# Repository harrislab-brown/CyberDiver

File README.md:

# CyberDiver: an untethered cyber-physical robotic impactor for water-entry experiments

This repository provides design source files and raw data to complement the article ([https://arxiv.org/abs/2503.20702](https://arxiv.org/abs/2503.20702)). 

# License

CyberDiver is licensed under the CC BY-SA 4.0 Creative Commons license.

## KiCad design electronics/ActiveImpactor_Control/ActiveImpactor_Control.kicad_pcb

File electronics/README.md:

# Electronics

This directory contains the KiCad design files, schematics, and Gerber files for the custom PCBs used in the CyberDiver. The control board and power board implement the majority of the functionality. The encoder daughterboard provides nose displacement measurements with an optical linear encoder (Celera CE300-40). The nose accelerometer board provides direct measurements of the impactor nose acceleration.

## Control board

## Power board

## Encoder daughter board

## Accelerometer daughter board

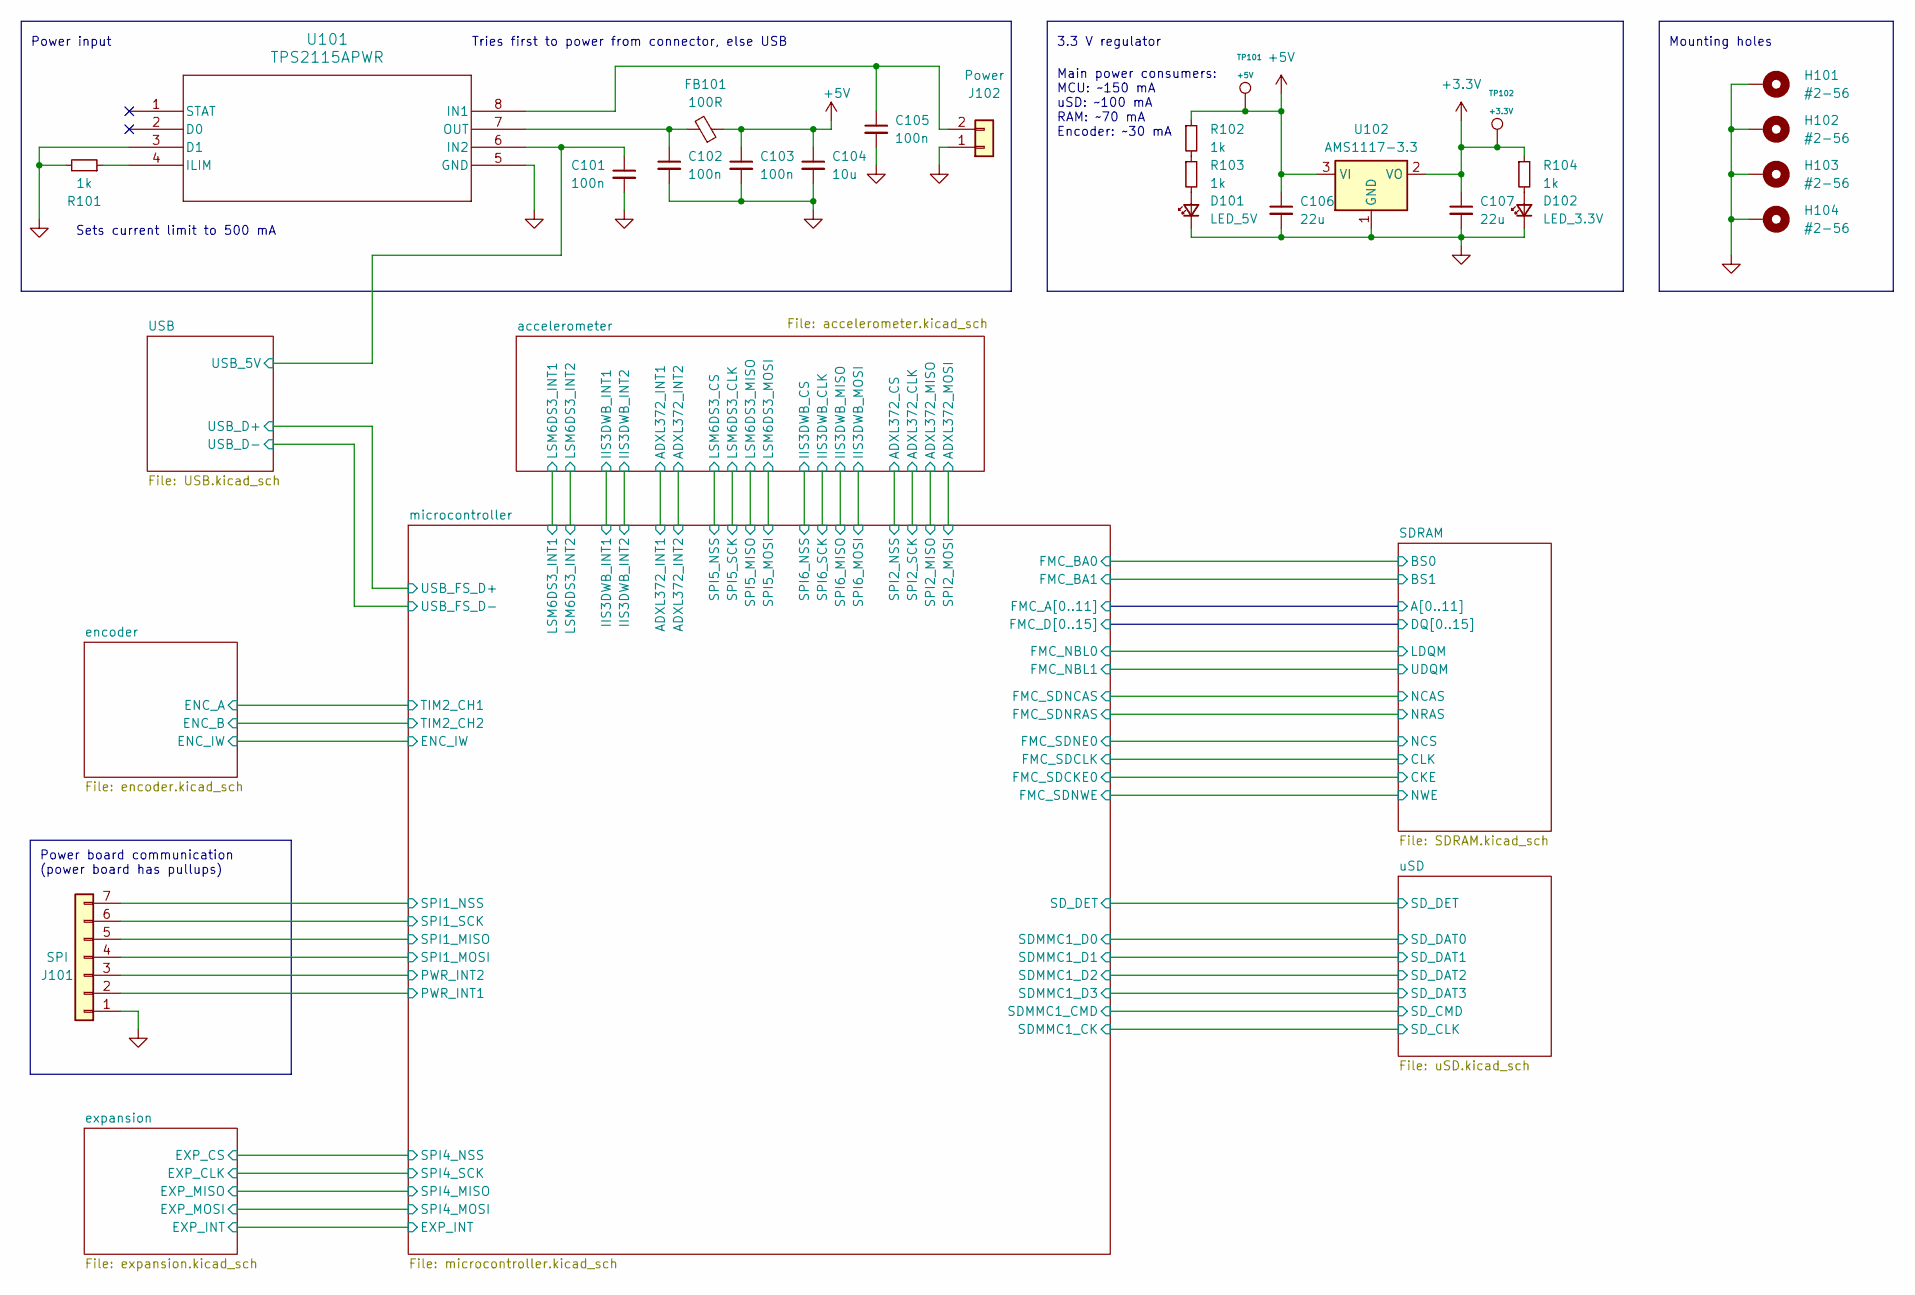
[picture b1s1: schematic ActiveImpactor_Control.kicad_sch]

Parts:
C101, C102, C103, C105: 100n; C_0402_1005Metric; LCSC C1525
C104: 10u; C_0603_1608Metric; LCSC C19702
C106, C107: 22u; C_0603_1608Metric; LCSC C2762594
D101: LED_5V; LED_0603_1608Metric; LCSC C965805
D102: LED_3.3V; LED_0603_1608Metric; LCSC C965805
FB101: 100R; L_0603_1608Metric; LCSC C1002
H101, H102, H103, H104: #2-56; MountingHole_2.5mm_Pad
J101: SPI; JST_SH_BM07B-SRSS-TB_1x07-1MP_P1.00mm_Vertical; Digikey 455-BM07B-SRSS-TBCT-ND
J102: Power; JST_PH_B2B-PH-SM4-TB_1x02-1MP_P2.00mm_Vertical; Digikey 455-B2B-PH-SM4-TBCT-ND
R101, R102, R103, R104: 1k; R_0402_1005Metric; LCSC C11702
TP101: +5V; TestPoint_Pad_D1.0mm
TP102: +3.3V; TestPoint_Pad_D1.0mm
U101: TPS2115APWR; TSSOP-8_4.4x3mm_P0.65mm; LCSC C70287
U102: AMS1117-3.3; SOT-223-3_TabPin2; LCSC C6186

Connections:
+3.3V: C107.1, R104.1, TP102.1, U102.2 (VO); also elsewhere on the board
+5V: C103.1, C104.1, C106.1, FB101.1, R102.1, TP101.1, U102.3 (VI); also elsewhere on the board
/USB/USB_5V: C101.1, U101.6 (IN2); also elsewhere on the board
/microcontroller/PWR_INT1: J101.2; also elsewhere on the board
/microcontroller/PWR_INT2: J101.3; also elsewhere on the board
/microcontroller/SPI1_MISO: J101.5; also elsewhere on the board
/microcontroller/SPI1_MOSI: J101.4; also elsewhere on the board
/microcontroller/SPI1_NSS: J101.7; also elsewhere on the board
/microcontroller/SPI1_SCK: J101.6; also elsewhere on the board
GND: C101.2, C102.2, C103.2, C104.2, C105.2, C106.2, C107.2, D101.1 (K), D102.1 (K), H101.1, H102.1, H103.1, H104.1, J101.1, J102.1, R101.2, U101.3 (D1), U101.5 (GND), U102.1 (GND); also elsewhere on the board
unnamed: D101.2 (A), R103.2
unnamed: D102.2 (A), R104.2
unnamed: C105.1, J102.2, U101.8 (IN1)
unnamed: R102.2, R103.1
unnamed: R101.1, U101.4 (ILIM)
unnamed: C102.1, FB101.2, U101.7 (OUT)

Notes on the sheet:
Mounting holes
Power input
Power board communication (power board has pullups)
Tries first to power from connector, else USB
Main power consumers: MCU: ~150 mA uSD: ~100 mA RAM: ~70 mA Encoder: ~30 mA
3.3 V regulator
Sets current limit to 500 mA

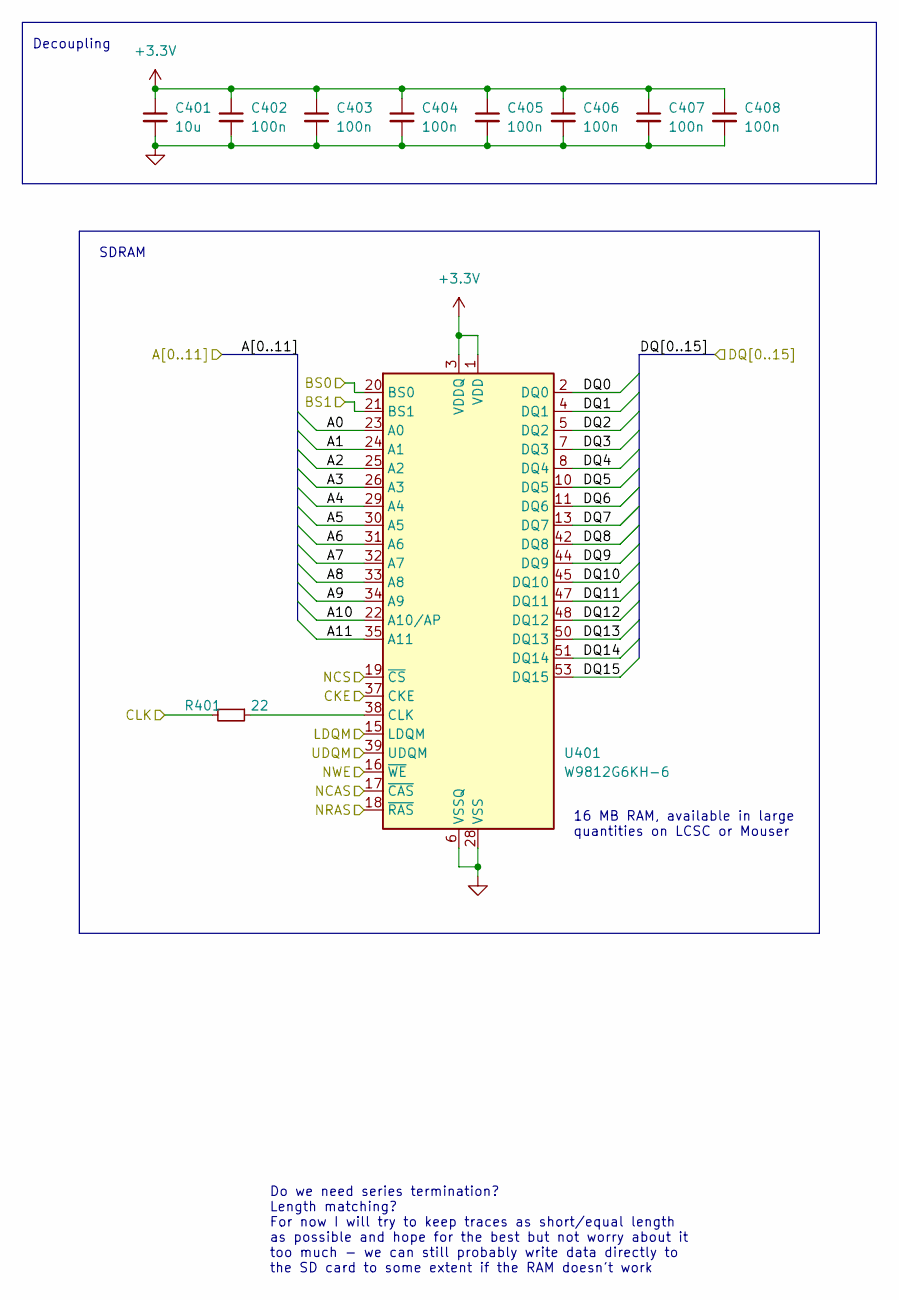
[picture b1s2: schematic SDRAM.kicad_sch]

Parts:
C401: 10u; C_0603_1608Metric; LCSC C19702
C402, C403, C404, C405, C406, C407, C408: 100n; C_0402_1005Metric; LCSC C1525
R401: 22; R_0402_1005Metric; LCSC C25092
U401: W9812G6KH-6; TSOP-II-54_22.2x10.16mm_P0.8mm; LCSC C62379

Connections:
+3.3V: C401.1, C402.1, C403.1, C404.1, C405.1, C406.1, C407.1, C408.1, U401.1 (VDD), U401.3 (VDDQ), U401.9 (VDDQ), U401.14 (VDD), U401.27 (VDD), U401.43 (VDDQ), U401.49 (VDDQ); also elsewhere on the board
/SDRAM/A0: U401.23 (A0); also elsewhere on the board
/SDRAM/A1: U401.24 (A1); also elsewhere on the board
/SDRAM/A2: U401.25 (A2); also elsewhere on the board
/SDRAM/A3: U401.26 (A3); also elsewhere on the board
/SDRAM/A4: U401.29 (A4); also elsewhere on the board
/SDRAM/A5: U401.30 (A5); also elsewhere on the board
/SDRAM/A6: U401.31 (A6); also elsewhere on the board
/SDRAM/A7: U401.32 (A7); also elsewhere on the board
/SDRAM/A8: U401.33 (A8); also elsewhere on the board
/SDRAM/A9: U401.34 (A9); also elsewhere on the board
/SDRAM/A10: U401.22 (A10/AP); also elsewhere on the board
/SDRAM/A11: U401.35 (A11); also elsewhere on the board
/SDRAM/BS0: U401.20 (BS0); also elsewhere on the board
/SDRAM/BS1: U401.21 (BS1); also elsewhere on the board
/SDRAM/CKE: U401.37 (CKE); also elsewhere on the board
/SDRAM/CLK: R401.2; also elsewhere on the board
/SDRAM/DQ0: U401.2 (DQ0); also elsewhere on the board
/SDRAM/DQ1: U401.4 (DQ1); also elsewhere on the board
/SDRAM/DQ2: U401.5 (DQ2); also elsewhere on the board
/SDRAM/DQ3: U401.7 (DQ3); also elsewhere on the board
/SDRAM/DQ4: U401.8 (DQ4); also elsewhere on the board
/SDRAM/DQ5: U401.10 (DQ5); also elsewhere on the board
/SDRAM/DQ6: U401.11 (DQ6); also elsewhere on the board
/SDRAM/DQ7: U401.13 (DQ7); also elsewhere on the board
/SDRAM/DQ8: U401.42 (DQ8); also elsewhere on the board
/SDRAM/DQ9: U401.44 (DQ9); also elsewhere on the board
/SDRAM/DQ10: U401.45 (DQ10); also elsewhere on the board
/SDRAM/DQ11: U401.47 (DQ11); also elsewhere on the board
/SDRAM/DQ12: U401.48 (DQ12); also elsewhere on the board
/SDRAM/DQ13: U401.50 (DQ13); also elsewhere on the board
/SDRAM/DQ14: U401.51 (DQ14); also elsewhere on the board
/SDRAM/DQ15: U401.53 (DQ15); also elsewhere on the board
/SDRAM/LDQM: U401.15 (LDQM); also elsewhere on the board
/SDRAM/NCAS: U401.17 (~CAS); also elsewhere on the board
/SDRAM/NCS: U401.19 (~CS); also elsewhere on the board
/SDRAM/NRAS: U401.18 (~RAS); also elsewhere on the board
/SDRAM/NWE: U401.16 (~WE); also elsewhere on the board
/SDRAM/UDQM: U401.39 (UDQM); also elsewhere on the board
GND: C401.2, C402.2, C403.2, C404.2, C405.2, C406.2, C407.2, C408.2, U401.6 (VSSQ), U401.12 (VSSQ), U401.28 (VSS), U401.41 (VSS), U401.46 (VSSQ), U401.52 (VSSQ), U401.54 (VSS); also elsewhere on the board
unnamed: R401.1, U401.38 (CLK)

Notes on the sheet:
SDRAM
Do we need series termination? Length matching? For now I will try to keep traces as short/equal length as possible and hope for the best but not worry about it too much - we can still probably write data directly to the SD card to some extent if the RAM doesn't work
16 MB RAM, available in large quantities on LCSC or Mouser
Decoupling

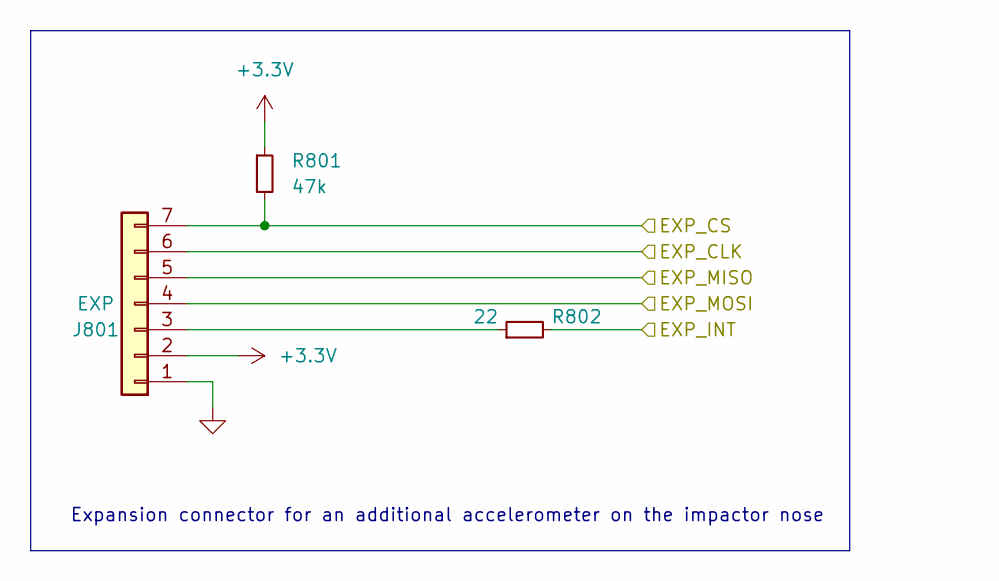
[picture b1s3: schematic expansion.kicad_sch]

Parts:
J801: EXP; JST_SH_SM07B-SRSS-TB_1x07-1MP_P1.00mm_Horizontal; LCSC C160406
R801: 47k; R_0402_1005Metric; LCSC C25792
R802: 22; R_0402_1005Metric; LCSC C25092

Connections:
+3.3V: J801.2, R801.1; also elsewhere on the board
/expansion/EXP_CLK: J801.6; also elsewhere on the board
/expansion/EXP_CS: J801.7, R801.2; also elsewhere on the board
/expansion/EXP_INT: R802.2; also elsewhere on the board
/expansion/EXP_MISO: J801.5; also elsewhere on the board
/expansion/EXP_MOSI: J801.4; also elsewhere on the board
GND: J801.1; also elsewhere on the board
unnamed: J801.3, R802.1

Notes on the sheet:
Expansion connector for an additional accelerometer on the impactor nose

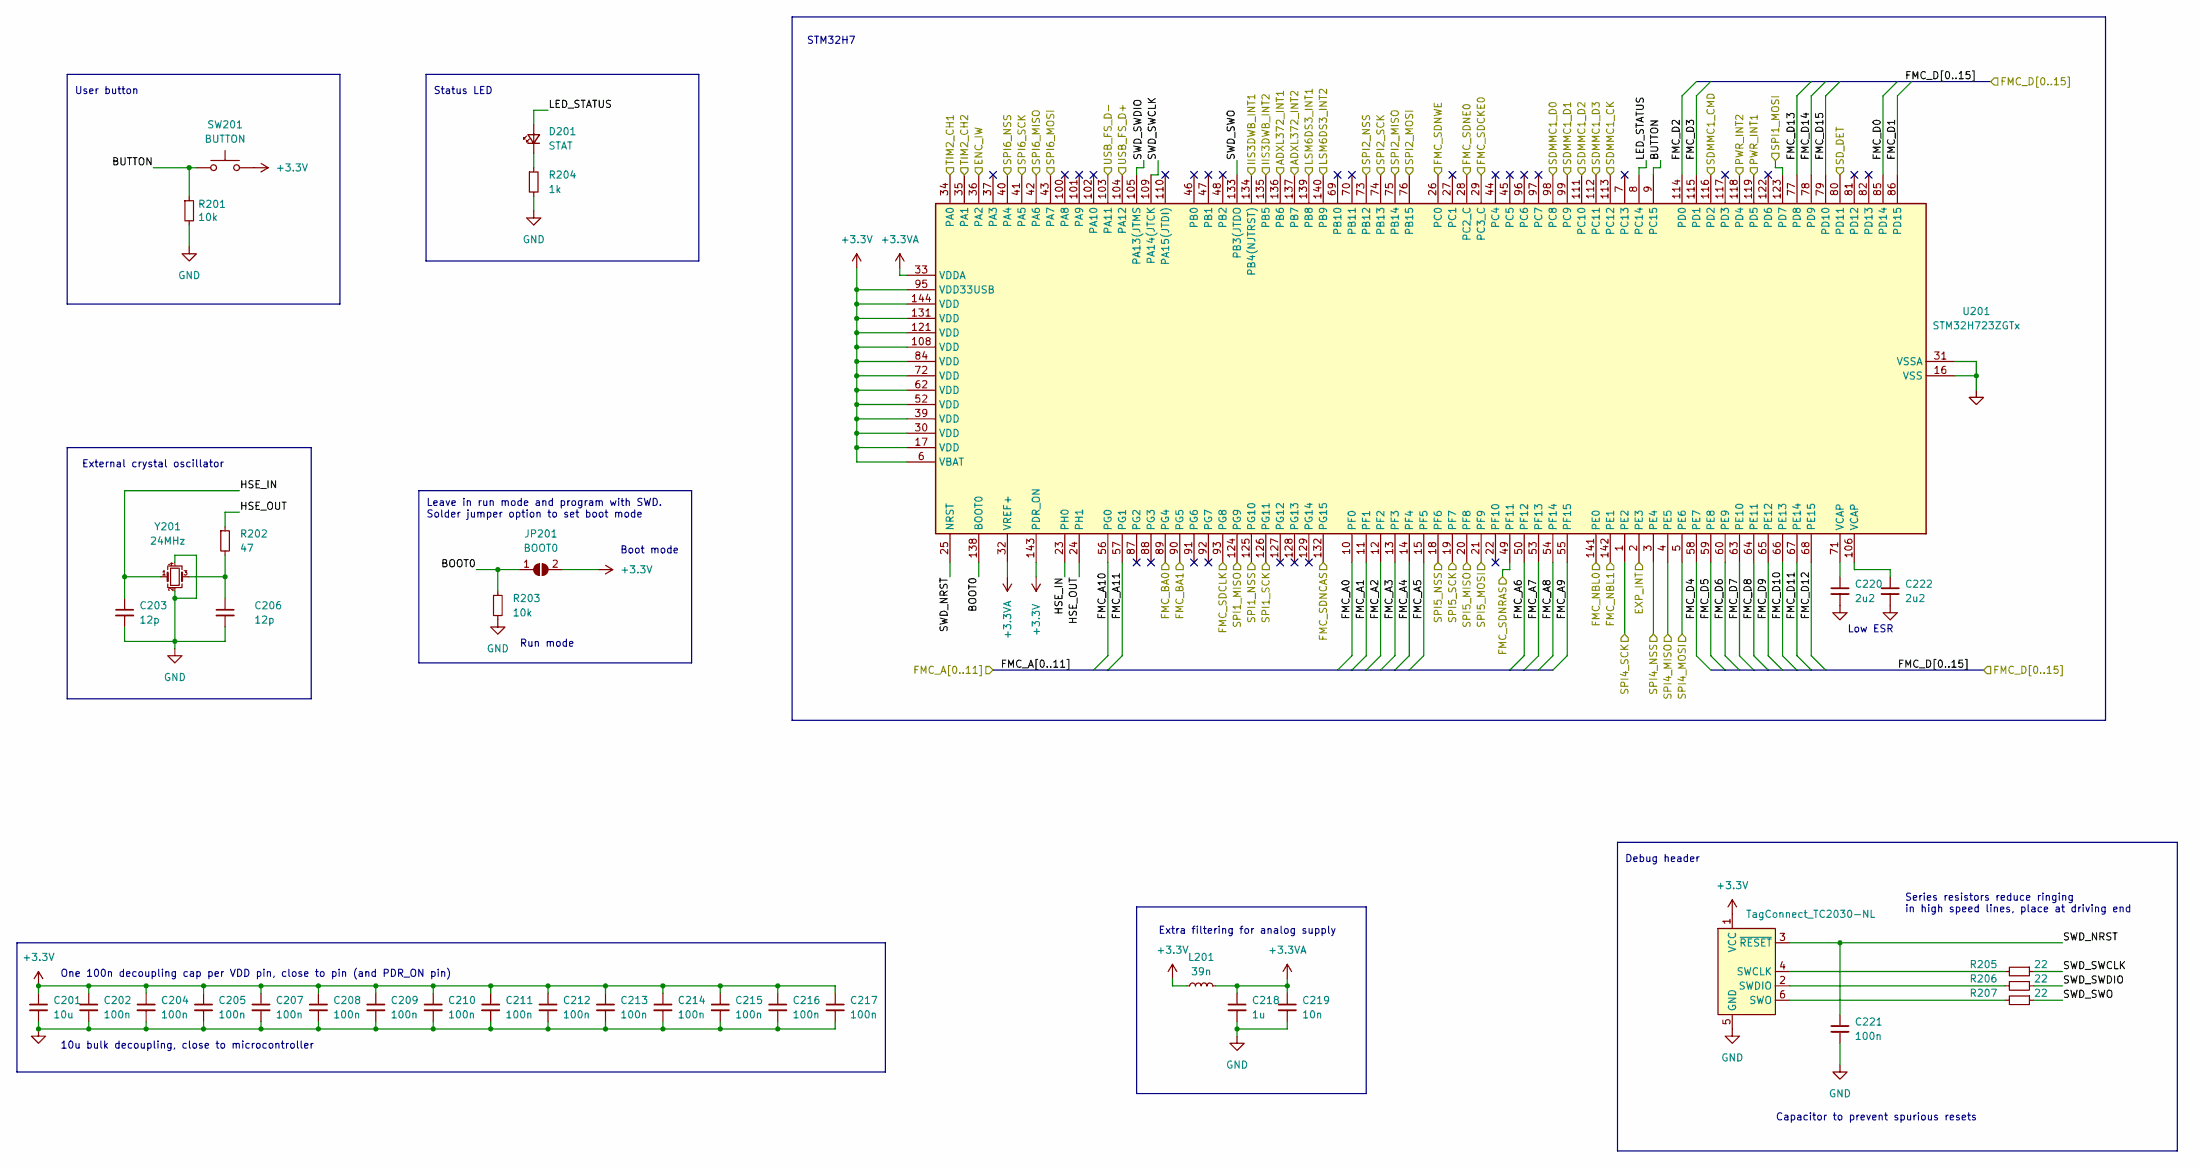
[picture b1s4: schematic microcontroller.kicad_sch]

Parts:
C201: 10u; C_0603_1608Metric; LCSC C19702
C202, C204, C205, C207, C208, C209, C210, C211, C212, C213, C214, C215, C216, C217, C221: 100n; C_0402_1005Metric; LCSC C1525
C203, C206: 12p; C_0402_1005Metric; LCSC C1547
C218: 1u; C_0402_1005Metric; LCSC C52923
C219: 10n; C_0402_1005Metric; LCSC C15195
C220, C222: 2u2; C_0603_1608Metric; LCSC C23630
D201: STAT; LED_0603_1608Metric; LCSC C84266
J201: TagConnect_TC2030-NL; Tag-Connect_TC2030-IDC-NL_2x03_P1.27mm_Vertical
JP201: BOOT0; SolderJumper-2_P1.3mm_Open_RoundedPad1.0x1.5mm
L201: 39n; L_0402_1005Metric; LCSC C26443
R201, R203: 10k; R_0402_1005Metric; LCSC C25744
R202: 47; R_0402_1005Metric; LCSC C25118
R204: 1k; R_0402_1005Metric; LCSC C11702
R205, R206, R207: 22; R_0402_1005Metric; LCSC C25092
SW201: BUTTON; SW_Push_SPST_NO_Alps_SKRK; LCSC C202388
U201: STM32H723ZGTx; LQFP-144_20x20mm_P0.5mm; LCSC C730146
Y201: 24MHz; Crystal_SMD_3225-4Pin_3.2x2.5mm; LCSC C70590

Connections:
+3.3V: C201.1, C202.1, C204.1, C205.1, C207.1, C208.1, C209.1, C210.1, C211.1, C212.1, C213.1, C214.1, C215.1, C216.1, C217.1, J201.1 (VCC), JP201.2 (B), L201.1, SW201.2, U201.6 (VBAT), U201.17 (VDD), U201.30 (VDD), U201.39 (VDD), U201.52 (VDD), U201.62 (VDD), U201.72 (VDD), U201.84 (VDD), U201.95 (VDD33USB), U201.108 (VDD), U201.121 (VDD), U201.131 (VDD), U201.143 (PDR_ON), U201.144 (VDD); also elsewhere on the board
+3.3VA: C218.1, C219.1, L201.2, U201.32 (VREF+), U201.33 (VDDA)
/SDRAM/A0: U201.10 (PF0); also elsewhere on the board
/SDRAM/A1: U201.11 (PF1); also elsewhere on the board
/SDRAM/A2: U201.12 (PF2); also elsewhere on the board
/SDRAM/A3: U201.13 (PF3); also elsewhere on the board
/SDRAM/A4: U201.14 (PF4); also elsewhere on the board
/SDRAM/A5: U201.15 (PF5); also elsewhere on the board
/SDRAM/A6: U201.50 (PF12); also elsewhere on the board
/SDRAM/A7: U201.53 (PF13); also elsewhere on the board
/SDRAM/A8: U201.54 (PF14); also elsewhere on the board
/SDRAM/A9: U201.55 (PF15); also elsewhere on the board
/SDRAM/A10: U201.56 (PG0); also elsewhere on the board
/SDRAM/A11: U201.57 (PG1); also elsewhere on the board
/SDRAM/BS0: U201.89 (PG4); also elsewhere on the board
/SDRAM/BS1: U201.90 (PG5); also elsewhere on the board
/SDRAM/CKE: U201.29 (PC3_C); also elsewhere on the board
/SDRAM/CLK: U201.93 (PG8); also elsewhere on the board
/SDRAM/DQ0: U201.85 (PD14); also elsewhere on the board
/SDRAM/DQ1: U201.86 (PD15); also elsewhere on the board
/SDRAM/DQ2: U201.114 (PD0); also elsewhere on the board
/SDRAM/DQ3: U201.115 (PD1); also elsewhere on the board
/SDRAM/DQ4: U201.58 (PE7); also elsewhere on the board
/SDRAM/DQ5: U201.59 (PE8); also elsewhere on the board
/SDRAM/DQ6: U201.60 (PE9); also elsewhere on the board
/SDRAM/DQ7: U201.63 (PE10); also elsewhere on the board
/SDRAM/DQ8: U201.64 (PE11); also elsewhere on the board
/SDRAM/DQ9: U201.65 (PE12); also elsewhere on the board
/SDRAM/DQ10: U201.66 (PE13); also elsewhere on the board
/SDRAM/DQ11: U201.67 (PE14); also elsewhere on the board
/SDRAM/DQ12: U201.68 (PE15); also elsewhere on the board
/SDRAM/DQ13: U201.77 (PD8); also elsewhere on the board
/SDRAM/DQ14: U201.78 (PD9); also elsewhere on the board
/SDRAM/DQ15: U201.79 (PD10); also elsewhere on the board
/SDRAM/LDQM: U201.141 (PE0); also elsewhere on the board
/SDRAM/NCAS: U201.132 (PG15); also elsewhere on the board
/SDRAM/NCS: U201.28 (PC2_C); also elsewhere on the board
/SDRAM/NRAS: U201.49 (PF11); also elsewhere on the board
/SDRAM/NWE: U201.26 (PC0); also elsewhere on the board
/SDRAM/UDQM: U201.142 (PE1); also elsewhere on the board
/USB/USB_D+: U201.104 (PA12); also elsewhere on the board
/USB/USB_D-: U201.103 (PA11); also elsewhere on the board
/accelerometer/ADXL372_CLK: U201.74 (PB13); also elsewhere on the board
/accelerometer/ADXL372_CS: U201.73 (PB12); also elsewhere on the board
/accelerometer/ADXL372_INT1: U201.136 (PB6); also elsewhere on the board
/accelerometer/ADXL372_INT2: U201.137 (PB7); also elsewhere on the board
/accelerometer/ADXL372_MISO: U201.75 (PB14); also elsewhere on the board
/accelerometer/ADXL372_MOSI: U201.76 (PB15); also elsewhere on the board
/accelerometer/IIS3DWB_CLK: U201.41 (PA5); also elsewhere on the board
/accelerometer/IIS3DWB_CS: U201.40 (PA4); also elsewhere on the board
/accelerometer/IIS3DWB_INT1: U201.134 (PB4(NJTRST)); also elsewhere on the board
/accelerometer/IIS3DWB_INT2: U201.135 (PB5); also elsewhere on the board
/accelerometer/IIS3DWB_MISO: U201.42 (PA6); also elsewhere on the board
/accelerometer/IIS3DWB_MOSI: U201.43 (PA7); also elsewhere on the board
/accelerometer/LSM6DS3_CLK: U201.19 (PF7); also elsewhere on the board
/accelerometer/LSM6DS3_CS: U201.18 (PF6); also elsewhere on the board
/accelerometer/LSM6DS3_INT1: U201.139 (PB8); also elsewhere on the board
/accelerometer/LSM6DS3_INT2: U201.140 (PB9); also elsewhere on the board
/accelerometer/LSM6DS3_MISO: U201.20 (PF8); also elsewhere on the board
/accelerometer/LSM6DS3_MOSI: U201.21 (PF9); also elsewhere on the board
/encoder/ENC_A: U201.34 (PA0); also elsewhere on the board
/encoder/ENC_B: U201.35 (PA1); also elsewhere on the board
/encoder/ENC_IW: U201.36 (PA2); also elsewhere on the board
/expansion/EXP_CLK: U201.1 (PE2); also elsewhere on the board
/expansion/EXP_CS: U201.3 (PE4); also elsewhere on the board
/expansion/EXP_INT: U201.2 (PE3); also elsewhere on the board
/expansion/EXP_MISO: U201.4 (PE5); also elsewhere on the board
/expansion/EXP_MOSI: U201.5 (PE6); also elsewhere on the board
/microcontroller/BOOT0: JP201.1 (A), R203.1, U201.138 (BOOT0)
/microcontroller/BUTTON: R201.1, SW201.1, U201.9 (PC15)
/microcontroller/HSE_IN: C203.1, U201.23 (PH0), Y201.1
/microcontroller/HSE_OUT: R202.1, U201.24 (PH1)
/microcontroller/LED_STATUS: D201.2 (A), U201.8 (PC14)
/microcontroller/PWR_INT1: U201.119 (PD5); also elsewhere on the board
/microcontroller/PWR_INT2: U201.118 (PD4); also elsewhere on the board
/microcontroller/SDMMC1_CK: U201.113 (PC12); also elsewhere on the board
/microcontroller/SDMMC1_CMD: U201.116 (PD2); also elsewhere on the board
/microcontroller/SDMMC1_D0: U201.98 (PC8); also elsewhere on the board
/microcontroller/SDMMC1_D1: U201.99 (PC9); also elsewhere on the board
/microcontroller/SDMMC1_D2: U201.111 (PC10); also elsewhere on the board
/microcontroller/SDMMC1_D3: U201.112 (PC11); also elsewhere on the board
/microcontroller/SD_DET: U201.80 (PD11); also elsewhere on the board
/microcontroller/SPI1_MISO: U201.124 (PG9); also elsewhere on the board
/microcontroller/SPI1_MOSI: U201.123 (PD7); also elsewhere on the board
/microcontroller/SPI1_NSS: U201.125 (PG10); also elsewhere on the board
/microcontroller/SPI1_SCK: U201.126 (PG11); also elsewhere on the board
/microcontroller/SWD_NRST: C221.1, J201.3 (~RESET), U201.25 (NRST)
/microcontroller/SWD_SWCLK: R205.1, U201.109 (PA14(JTCK)
/microcontroller/SWD_SWDIO: R206.1, U201.105 (PA13(JTMS)
/microcontroller/SWD_SWO: R207.1, U201.133 (PB3(JTDO)
GND: C201.2, C202.2, C203.2, C204.2, C205.2, C206.2, C207.2, C208.2, C209.2, C210.2, C211.2, C212.2, C213.2, C214.2, C215.2, C216.2, C217.2, C218.2, C219.2, C220.2, C221.2, C222.2, J201.5 (GND), R201.2, R203.2, R204.2, U201.16 (VSS), U201.31 (VSSA), U201.38 (VSS), U201.51 (VSS), U201.61 (VSS), U201.83 (VSS), U201.94 (VSS), U201.107 (VSS), U201.120 (VSS), U201.130 (VSS), Y201.2, Y201.4; also elsewhere on the board
unnamed: C206.1, R202.2, Y201.3
unnamed: C220.1, U201.71 (VCAP)
unnamed: C222.1, U201.106 (VCAP)
unnamed: D201.1 (K), R204.1
unnamed: J201.4 (SWCLK), R205.2
unnamed: J201.2 (SWDIO), R206.2
unnamed: J201.6 (SWO), R207.2

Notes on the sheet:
Debug header
Run mode
Leave in run mode and program with SWD. Solder jumper option to set boot mode
User button
Low ESR
Extra filtering for analog supply
One 100n decoupling cap per VDD pin, close to pin (and PDR_ON pin)
Boot mode
Status LED
External crystal oscillator
Capacitor to prevent spurious resets
STM32H7
Series resistors reduce ringing in high speed lines, place at driving end
10u bulk decoupling, close to microcontroller

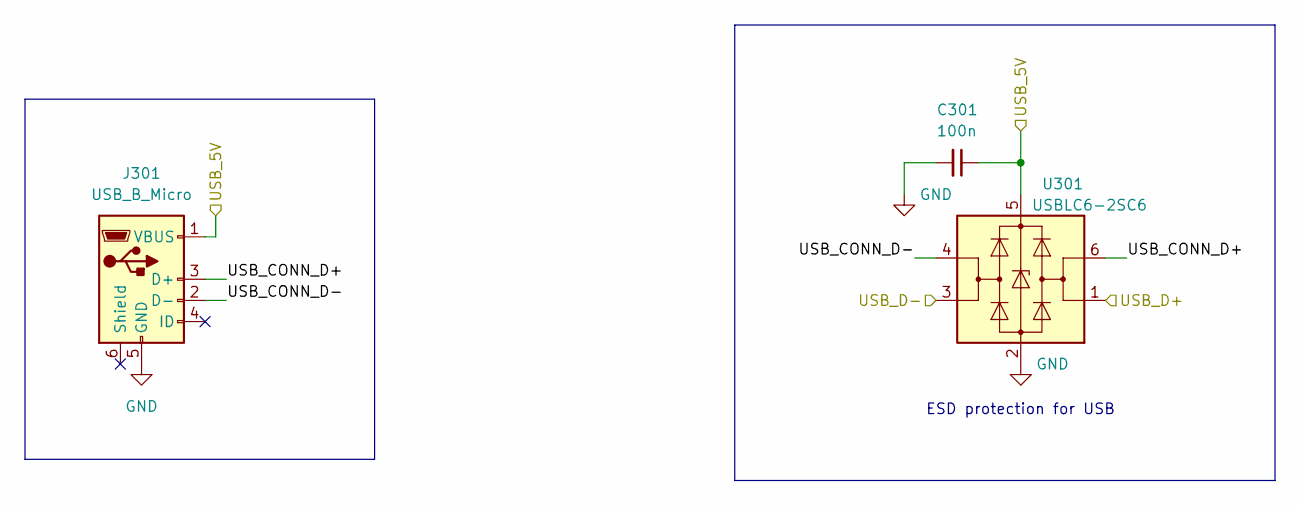
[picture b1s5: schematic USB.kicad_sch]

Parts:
C301: 100n; C_0402_1005Metric; LCSC C1525
J301: USB_B_Micro; MicroXNJ; LCSC C404969
U301: USBLC6-2SC6; SOT-23-6; LCSC C2827654

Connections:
/USB/USB_5V: C301.1, J301.1 (VBUS), U301.5 (VBUS); also elsewhere on the board
/USB/USB_CONN_D+: J301.3 (D+), U301.6 (I/O1)
/USB/USB_CONN_D-: J301.2 (D-), U301.4 (I/O2)
/USB/USB_D+: U301.1 (I/O1); also elsewhere on the board
/USB/USB_D-: U301.3 (I/O2); also elsewhere on the board
GND: C301.2, J301.5 (GND), U301.2 (GND); also elsewhere on the board

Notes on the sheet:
ESD protection for USB

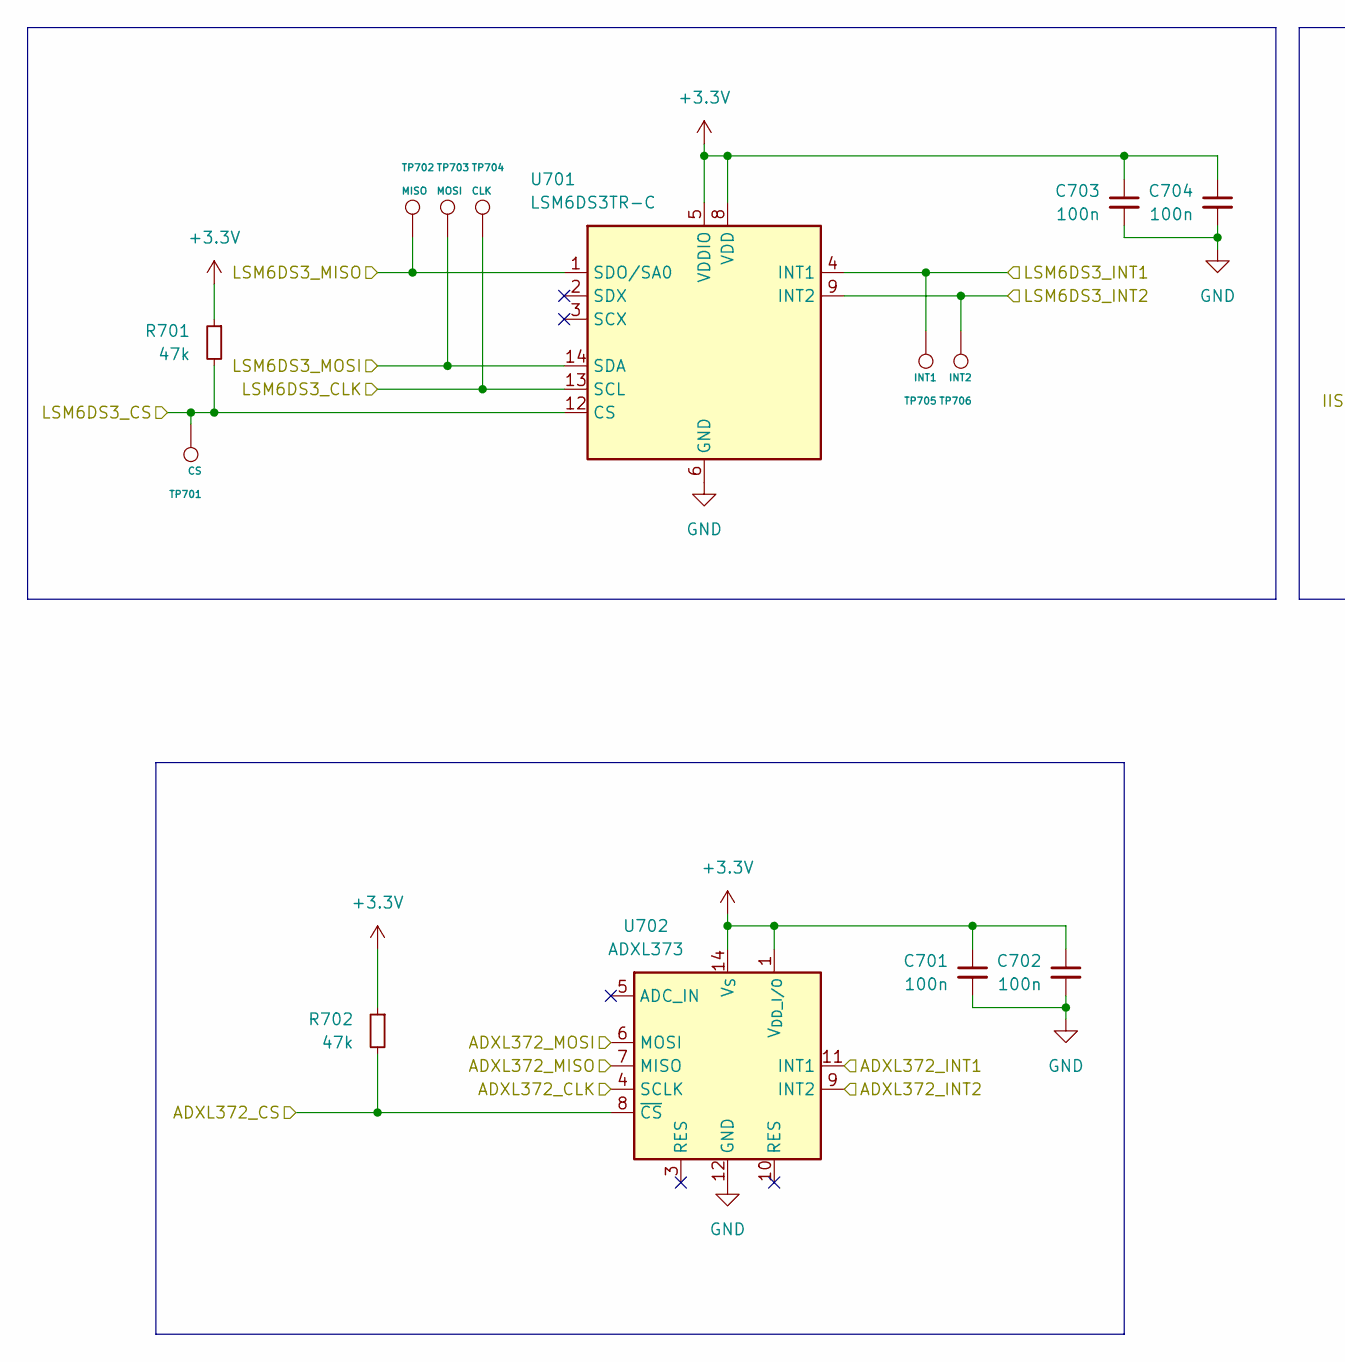
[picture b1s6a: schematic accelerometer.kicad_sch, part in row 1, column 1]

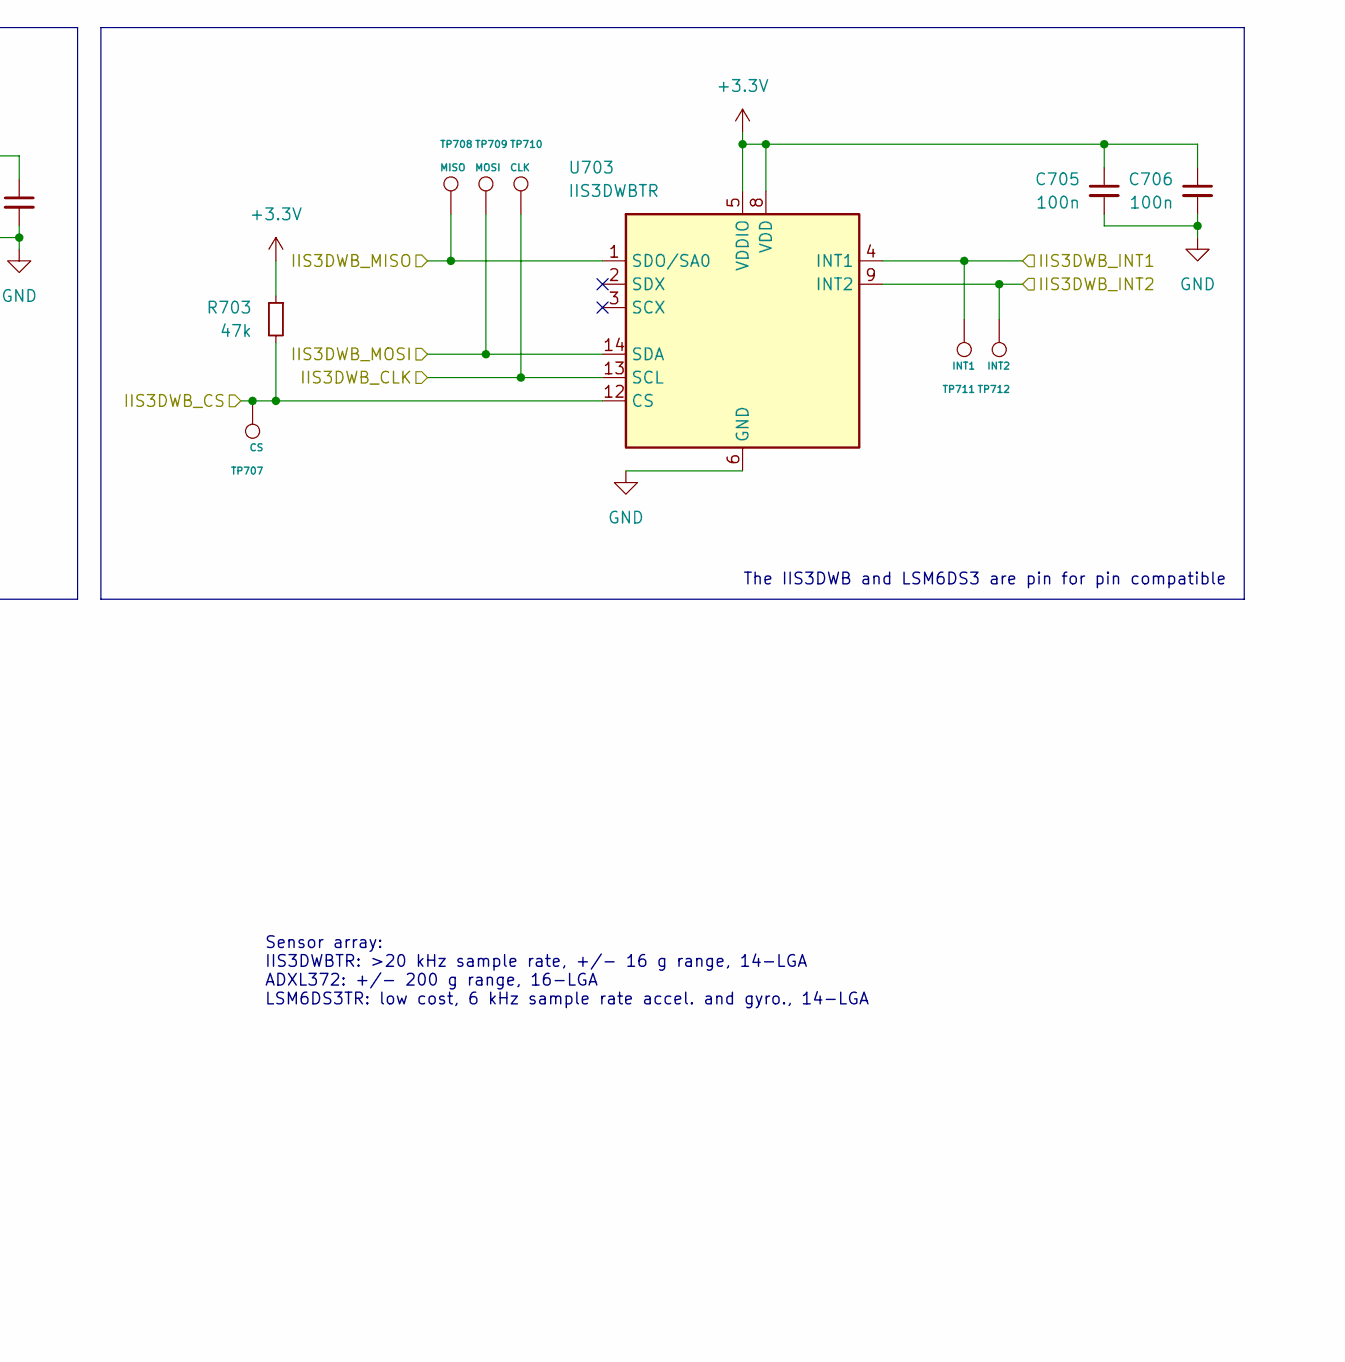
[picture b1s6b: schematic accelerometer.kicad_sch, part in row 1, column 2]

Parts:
C701, C702, C703, C704, C705, C706: 100n; C_0402_1005Metric; LCSC C1525
R701, R702, R703: 47k; R_0402_1005Metric; LCSC C25792
TP701, TP707: CS; TestPoint_Pad_D1.0mm
TP702, TP708: MISO; TestPoint_Pad_D1.0mm
TP703, TP709: MOSI; TestPoint_Pad_D1.0mm
TP704, TP710: CLK; TestPoint_Pad_D1.0mm
TP705, TP711: INT1; TestPoint_Pad_D1.0mm
TP706, TP712: INT2; TestPoint_Pad_D1.0mm
U701: LSM6DS3TR-C; LGA-14_3x2.5mm_P0.5mm_LayoutBorder3x4y; LCSC C967633
U702: ADXL373; Analog_LGA-16_3.25x3mm_P0.5mm_LayoutBorder3x5y; LCSC C3216386
U703: IIS3DWBTR; LGA-14_3x2.5mm_P0.5mm_LayoutBorder3x4y; LCSC C717702

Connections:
+3.3V: C701.1, C702.1, C703.1, C704.1, C705.1, C706.1, R701.1, R702.1, R703.1, U701.5 (VDDIO), U701.8 (VDD), U702.1 (V_{DD_I/O}), U702.14 (V_{S}), U703.5 (VDDIO), U703.8 (VDD); also elsewhere on the board
/accelerometer/ADXL372_CLK: U702.4 (SCLK); also elsewhere on the board
/accelerometer/ADXL372_CS: R702.2, U702.8 (~CS); also elsewhere on the board
/accelerometer/ADXL372_INT1: U702.11 (INT1); also elsewhere on the board
/accelerometer/ADXL372_INT2: U702.9 (INT2); also elsewhere on the board
/accelerometer/ADXL372_MISO: U702.7 (MISO); also elsewhere on the board
/accelerometer/ADXL372_MOSI: U702.6 (MOSI); also elsewhere on the board
/accelerometer/IIS3DWB_CLK: TP710.1, U703.13 (SCL); also elsewhere on the board
/accelerometer/IIS3DWB_CS: R703.2, TP707.1, U703.12 (CS); also elsewhere on the board
/accelerometer/IIS3DWB_INT1: TP711.1, U703.4 (INT1); also elsewhere on the board
/accelerometer/IIS3DWB_INT2: TP712.1, U703.9 (INT2); also elsewhere on the board
/accelerometer/IIS3DWB_MISO: TP708.1, U703.1 (SDO/SA0); also elsewhere on the board
/accelerometer/IIS3DWB_MOSI: TP709.1, U703.14 (SDA); also elsewhere on the board
/accelerometer/LSM6DS3_CLK: TP704.1, U701.13 (SCL); also elsewhere on the board
/accelerometer/LSM6DS3_CS: R701.2, TP701.1, U701.12 (CS); also elsewhere on the board
/accelerometer/LSM6DS3_INT1: TP705.1, U701.4 (INT1); also elsewhere on the board
/accelerometer/LSM6DS3_INT2: TP706.1, U701.9 (INT2); also elsewhere on the board
/accelerometer/LSM6DS3_MISO: TP702.1, U701.1 (SDO/SA0); also elsewhere on the board
/accelerometer/LSM6DS3_MOSI: TP703.1, U701.14 (SDA); also elsewhere on the board
GND: C701.2, C702.2, C703.2, C704.2, C705.2, C706.2, U701.6 (GND), U701.7 (GND), U702.12 (GND), U702.13 (GND), U702.16 (GND), U703.6 (GND), U703.7 (GND); also elsewhere on the board

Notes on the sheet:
Sensor array: IIS3DWBTR: >20 kHz sample rate, +/- 16 g range, 14-LGA ADXL372: +/- 200 g range, 16-LGA LSM6DS3TR: low cost, 6 kHz sample rate accel. and gyro., 14-LGA
The IIS3DWB and LSM6DS3 are pin for pin compatible
